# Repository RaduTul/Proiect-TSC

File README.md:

# Proiect-TSC 
Tulumb Radu Cristian 332CB
e-book reader

Procesul de dezvoltare
In prima parte a proiectului cand am realizat schematicul m-am folosit de descrierea pieselor din pdf-ul de pe OCW pentru a denumi, aranja si a da valori componentelor. Am schimbat de fiecare data layerul cand ba puneam nets ba symbols ba lines. M-am folosit de toolurile necesare pentru a schimba numele si valorile pieselor apoi am dat switch in PCB.
In PCB am tinut cont de masuratorile de pe OCW si de pozitia componentelor. Ca sa ma asigur ca dimensiunea placutei este corecta am modificat gridul PCB-ului in 1 mm cu 1 mm pentru a determina daca este dimensiunea corecta. Rutarea a fost mai complicata, dar am reusit sa o fac pe layerul de top si bottom. Mai aveam doua erori hole carora le-am dat approve. Pentru a continua am dat switch in PCB3D.
Am cautat piesele individual folosind design manager si sintaxa (ObjectType = Device) AND (Name = "piesa respectiva") pentru a cauta piesa pentru care urma sa fac un model 3D. Modelele 3D au fost luate de pe SnapMagic, Mouser, SnapEDA si componentsearchengine unde am gasit modelele 3D pentru fiecare piesa in parte. Am creat un fisier special cu toate modelele 3D necesare, le-am rotit si ajustat pentru a se incadra in linia punctata verde si intre cele doua puncte verzi si i-am dat replace package apoi am salvat, am dat in PCB update apoi cand dadeam switch to PCB3D imi punea piesa pe placuta. Pentru TP-uri am desenat un cerc.
Pentru generarea fisierelor Gerber am folosit optiunea de Fabrication Outputs din meniul MANUFACTURE din Fusion 360. Am selectat toate straturile necesare (Top Copper, Bottom Copper, Top Mask, Bottom Mask, Top Paste, Bottom Paste, Top Silkscreen, Bottom Silkscreen si Edge Cuts) si am generat fisierele in formatul cerut.
Am generat fisierul BOM (Bill of Materials) utilizand functionalitatea din meniul MANAGE, selectand toate componentele folosite in proiect si exportand in formatul CSV, apoi l-am salvat in directorul Manufacturing.
Fisierul Pick and Place (CPL) a fost generat din meniul MANUFACTURE, sectiunea Assembly, selectand optiunile pentru coordonatele componentelor si formatand corespunzator pentru productie.
Probleme la implementare
Aprobarea erorilor
La rutarea PCB-ului a fost nevoie sa aprob 2 erori de "hole" cauzate de componentele SMD.
Lipsa model 3D
Pentru TP-uri nu am gasit un model 3D, asa ca am facut un cerc pe care l-am ridicat putin.

[(BOM)](Manufacturing/BOM_proiect2025%20v19.csv)

## Functionalitatile Hardware
Acest e-book reader foloseste un microcontroller ESP32-C6 WROOM care controleaza un display e-ink de 7.5" cu rezolutie 800x480px. Dispozitivul include urmatoarele componente principale:
Componente Hardware Utilizate

ESP32-C6: Microcontroller principal pentru procesarea datelor si conectivitate.
E-Paper Display 7.5": Display cu consum redus de energie, conectat prin SPI.
Conectori pentru SD Card: Permite stocarea suplimentara a cartilor electronice.
Memorie NOR Flash W25Q512: Stocare suplimentara pentru fisiere tip e-book.
Baterie Li-Po: Sursa principala de alimentare a dispozitivului.
Conector USB-C: Permite incarcarea si transferul de date.
Modul RTC DS3231SN: Functionalitate de ceas in timp real.
Senzor BME680: Monitorizeaza temperatura si umiditate prin interfata I2C.
MAX17048G: Circuit de management pentru baterie.

## Interfete Principale

SPI: Utilizata pentru E-Paper display si memoria Flash.
I2C: Conecteaza senzorul BME680 si modulul RTC.
GPIO: Utilizati pentru butoane si alte componente periferice.

## Pini Utilizati - ESP32-C6

GPIO6 (IO6): SCK pentru interfata SPI (inlocuieste GPIO3/GPIO18/GPIO19 din listarea initiala).
GPIO2 (IO2): MISO pentru interfata SPI.
GPIO7 (IO7): MOSI pentru interfata SPI (inlocuieste GPIO1 din listarea initiala).
GPIO11 (IO11): Chip Select pentru memoria Flash (inlocuieste GPIO5 din listarea initiala).
GPIO3 (IO3): Reset pentru E-Paper (inlocuieste GPIO4 din listarea initiala).
GPIO4 (IO4): Chip Select pentru cardul SD (inlocuieste GPIO10 din listarea initiala).
GPIO22 (IO22): SCL pentru interfata I2C.
GPIO21 (IO21): SDA pentru interfata I2C.
GPIO16 (IO16): TX pentru comunicatie seriala.
GPIO17 (IO17): RX pentru comunicatie seriala.
GPIO20 (IO20): Conectat la butonul BOOT.
GPIO21 (IO21): Conectat la butonul RESET (posibil duplicat cu SDA, necesita verificare in schematic).
GPIO22 (IO22): Conectat la butonul CHANGE (posibil duplicat cu SCL, necesita verificare in schematic).

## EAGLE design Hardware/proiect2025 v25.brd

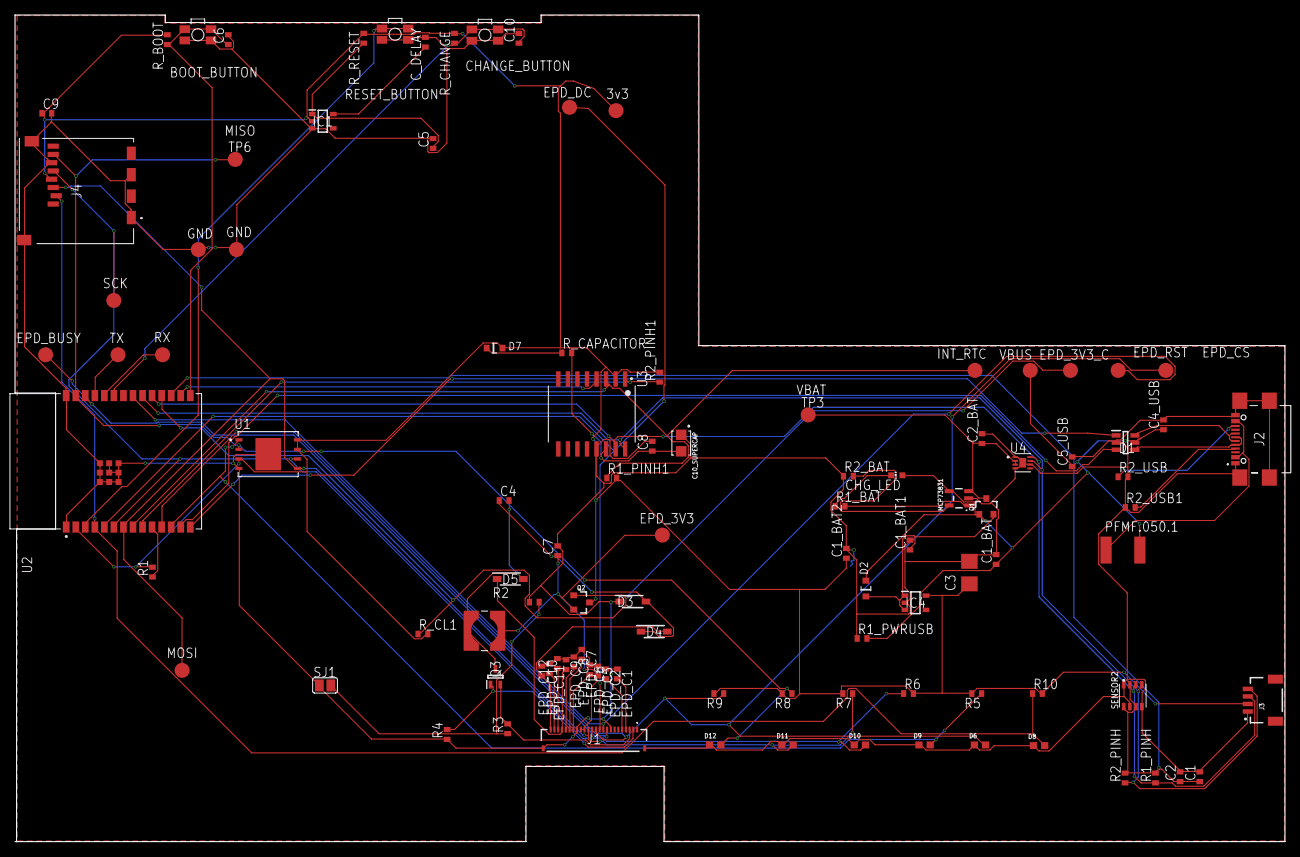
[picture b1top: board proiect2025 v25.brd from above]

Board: 2 copper layers, 169.0 x 110.0 mm, 103 parts (0 on the bottom side), 55 nets.

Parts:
BOOT_BUTTON: BUTTON_CUSYOMV1; MYBUTTON
C1, C2, C4_USB, C6, C8, C9, C10: 100nF; EAGLE-LTSPICE_C0402
C1_BAT, C1_BAT1, C1_BAT2, C2_BAT, C5_USB: 4.7uF; EAGLE-LTSPICE_C0402
C3: 100uF TANT; RCL_CT3528
C4: 4.7uF/25V; EAGLE-LTSPICE_C0402
C5: 1uF; EAGLE-LTSPICE_C0402
C7: 10uF; EAGLE-LTSPICE_C0402
C10_SUPERCAP: CPH3225A; CAPCP3225X100N
CHANGE_BUTTON: BUTTON_CUSYOMV1; MYBUTTON
CHG_LED: -; ADAFRUIT_CHIP-LED0603
C_DELAY: 100nF; EAGLE-LTSPICE_C0402
D1: USBLC6-2SC6Y; SOT95P280X145-6N
D2, D7: ESP32_WROVER_AVX---SD0805S020S1R0_AVX_SD0805S020S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; ESP32_WROVER_AVX---SD0805S020S1R0_AVX_SD0805S020S1R0_0
D3, D4, D5: MBR0530; SOD3716X135N
D6, D8, D9, D10, D11, D12: PGB1010603MR; DIOC1608X36N
EPD_C1, EPD_C2, EPD_C6, EPD_C7, EPD_C8, EPD_C9, EPD_C10, EPD_C11, EPD_C12: 1uF/50V; EAGLE-LTSPICE_C0402
EPD_C5: 0.1uF/50V; EAGLE-LTSPICE_C0402
IC1: BD5229G-TR; SOT95P280X125-5N
IC4: XC6220A331MR-G; SOT95P280X120-5N
J1: FH34SRJ-24S-0.5SH_99_; FH34SRJ24S05SH99
J2: SAMACSYS_PARTS_USB4110-GF-A; SAMACSYS_PARTS_USB4110GFA
J3: QWIIC_RIGHT_ANGLE; JST04_1MM_RA
J4: 112A-TAAR-R03_ATTEND; 112ATAARR03ATTEND
L1: 68uH; IND_4828-WE-TPC_WRE
MCP73831: ESP32_WROVER_SPARKFUN-IC-POWER_MCP73831; ESP32_WROVER_SPARKFUN-IC-POWER_SOT23-5
PFMF.050.1: ESP32C6_VARISTORCN1812; ESP32C6_VARISTOR_CT/CN1812
Q1, Q2: 20V/4.2A/52mΩ/1.4W; ESP32_WROVER_SPARKFUN-DISCRETESEMI_SOT23-3
Q3: SI1308EDL-T1-GE3; SOT65P210X110-3N
R1, R1_PINH, R1_PINH1, R2_PINH, R2_PINH1, R5, R6, R7, R8, R9, R10: 10K; ESP32_WROVER_EAGLE-LTSPICE_R0402
R1_BAT: 200; ESP32_WROVER_EAGLE-LTSPICE_R0402
R1_PWRUSB: 100k; ESP32_WROVER_EAGLE-LTSPICE_R0402
R2: 2.2; ESP32_WROVER_EAGLE-LTSPICE_R0402
R2_BAT: 2k; ESP32_WROVER_EAGLE-LTSPICE_R0402
R2_USB, R2_USB1: 5k1; ESP32_WROVER_EAGLE-LTSPICE_R0402
R3: 0.47; ESP32_WROVER_EAGLE-LTSPICE_R0402
R4: 10k; ESP32_WROVER_EAGLE-LTSPICE_R0402
RESET_BUTTON: BUTTON_CUSYOMV1; MYBUTTON
R_BOOT: 10K; ESP32_WROVER_EAGLE-LTSPICE_R0402
R_CAPACITOR: 15; ESP32_WROVER_EAGLE-LTSPICE_R0402
R_CHANGE: 10K; ESP32_WROVER_EAGLE-LTSPICE_R0402
R_CL1: 10K; ESP32_WROVER_EAGLE-LTSPICE_R0402
R_RESET: 10K; ESP32_WROVER_EAGLE-LTSPICE_R0402
SENSOR2: ESP32_WROVER_BME680_BME680; ESP32_WROVER_BME680_PSON80P300X300X100-8N
SJ1: -; SJ
TP1, TP2, TP3, TP4, TP5, TP6, TP7, TP8, TP9, TP10, TP11, TP12, TP13, TP14, TP15, TP16, TP17: TPTP20R; TP20R
U1: W25Q512JVEIQ; SON127P600X800X80-9N
U2: ESP32-C6-WROOM-1-N8; XCVR_ESP32-C6-WROOM-1-N8
U3: DS3231SN#; SOIC127P1032X265-16N
U4: MAX17048G+T10; SON50P200X200X80-9N

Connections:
3V3: C1_BAT2.1, C3.+, C9.1, D7.2, IC1.2, IC4.5, J3.2, J4.P4, Q2.3, R1.2, R1_PINH1.2, R2_PINH1.2, R5.2, R6.2, R7.2, R8.2, R9.2, R10.2, R_BOOT.2, R_CHANGE.2, R_CL1.2, R_RESET.2, TP16.TP, U1.3, U1.7, U1.8, U2.2, U3.2
32KHZ: R2_PINH1.1, U2.9, U3.1
DN: D1.4, J2.A7, J2.B7
DP: D1.6, J2.A6, J2.B6
EPD_3V3: C7.1, EPD_C5.2, J1.15, J1.16, L1.2, Q2.2, TP17.TP
EPD_3V3_C: Q2.1, R_CL1.1, TP13.TP, U2.18
EPD_BUSY: J1.9, TP9.TP, U2.26
EPD_CS: D6.2, J1.12, R9.1, TP10.TP, U2.11
EPD_DC: J1.11, TP11.TP, U2.5
EPD_RST: J1.10, TP12.TP, U2.21
FLASH_CS: D9.2, R5.1, U1.1, U2.12
GDR: J1.2, Q3.1, R4.2
GND: BOOT_BUTTON.1, BOOT_BUTTON.2, C1.2, C1_BAT.2, C1_BAT1.2, C1_BAT2.2, C2.2, C2_BAT.2, C3.-, C4_USB.2, C5.2, C5_USB.2, C6.2, C7.2, C8.2, C9.2, C10.2, C10_SUPERCAP.1, CHANGE_BUTTON.1, CHANGE_BUTTON.2, C_DELAY.2, D1.2, D3.1, D6.1, D8.1, D9.1, D10.1, D11.1, D12.1, EPD_C1.1, EPD_C2.1, EPD_C5.1, EPD_C6.1, EPD_C7.1, EPD_C8.1, EPD_C9.1, EPD_C10.1, EPD_C11.1, EPD_C12.1, IC1.3, IC4.2, J1.8, J1.17, J1.MP1, J1.MP2, J2.A1, J2.A12, J2.B1, J2.B12, J2.MP1, J2.MP2, J2.MP3, J2.MP4, J3.1, J4.G1, J4.G2, J4.G3, J4.G4, J4.P6, MCP73831.2, R1_PWRUSB.1, R2.1, R2_BAT.1, R2_USB.2, R2_USB1.1, R4.1, RESET_BUTTON.1, RESET_BUTTON.2, SENSOR2.1, SENSOR2.5, SENSOR2.7, SJ1.1, TP4.TP, TP5.TP, U1.4, U1.9, U2.1, U2.28, U2.29_1, U2.29_2, U2.29_3, U2.29_4, U2.29_5, U2.29_6, U2.29_7, U2.29_8, U2.29_9, U3.13, U4.1, U4.4, U4.6, U4.9
GPIO8: R1.1, U2.10
I2C_PW: C1.1, C2.1, R1_PINH.2, R2_PINH.2, SENSOR2.2, SENSOR2.6, SENSOR2.8, U2.17
INT_RTC: R1_PINH1.1, TP15.TP, U2.8, U3.3
IO/BOOT: BOOT_BUTTON.3, BOOT_BUTTON.4, C6.1, R_BOOT.1, U2.15
IO/CHANGE: C10.1, CHANGE_BUTTON.3, CHANGE_BUTTON.4, R_CHANGE.1, U2.23
MISO: D12.2, J4.P7, R8.1, TP6.TP, U1.2, U2.27
MOSI: D11.2, J1.14, J4.P3, R7.1, TP7.TP, U1.5, U2.7
unnamed: J2.A5, R2_USB1.2
unnamed: EPD_C12.2, J1.24
unnamed: C1_BAT1.1, D2.1, IC4.1, IC4.3, Q1.2
unnamed: C4.1, D3.2, D4.1
unnamed: CHG_LED.C, R1_BAT.1
unnamed: MCP73831.1, R1_BAT.2
unnamed: J2.B5, R2_USB.1
unnamed: MCP73831.5, R2_BAT.2
unnamed: C_DELAY.1, IC1.5
unnamed: EPD_C10.2, J1.22
unnamed: EPD_C8.2, J1.20
unnamed: EPD_C7.2, J1.19
unnamed: EPD_C6.2, J1.18
unnamed: D7.1, R_CAPACITOR.1
unnamed: EPD_C2.2, J1.5
unnamed: EPD_C1.2, J1.4
PREVGH: D5.1, EPD_C9.2, J1.21
PREVGL: D4.2, EPD_C11.2, J1.23
RESE: J1.3, Q3.2, R3.2
RESE': R2.2, R3.1, SJ1.2
RESET: C5.1, IC1.1, RESET_BUTTON.3, RESET_BUTTON.4, R_RESET.1, U2.3
RTC_RST: U2.16, U3.4
RX: TP2.TP, U2.24
SCK: D10.2, J1.13, J4.P5, R6.1, TP8.TP, U1.6, U2.6
SCL: J3.4, R2_PINH.1, SENSOR2.4, U2.20, U3.16, U4.7
SDA: J3.3, R1_PINH.1, SENSOR2.3, U2.19, U3.15, U4.8
SRC: C4.2, D5.2, L1.1, Q3.3
SS_SD: D8.2, J4.P2, R10.1, U2.4
TX: TP1.TP, U2.25
USB_D+: D1.1, U2.14
USB_D-: D1.3, U2.13
VBAT: C2_BAT.1, MCP73831.3, Q1.3, TP3.TP, U4.2, U4.3
VBUS: C1_BAT.1, C4_USB.1, C5_USB.1, CHG_LED.A, D1.5, D2.2, MCP73831.4, PFMF.050.1.2, Q1.1, R1_PWRUSB.2, TP14.TP
VRTC: C8.1, C10_SUPERCAP.2, R_CAPACITOR.2, U3.14
VUSB: J2.A4, J2.A9, J2.B4, J2.B9, PFMF.050.1.1

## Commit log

2025-04-06 Create LICENSE
2025-04-06 Upload Project
2025-04-06 Done
    Done
2025-04-06 Done
2025-04-11 Fix after review
2025-04-12 Solved issues

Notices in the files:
parts and their libraries:
COPYRIGHT: Copyright (C) 2024 Ultra Librarian. All rights reserved.
